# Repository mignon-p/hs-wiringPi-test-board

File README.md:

This is a simple add-on board for [Raspberry Pi][1].  It is meant for
testing the [Haskell binding for wiringPi][2].  It connects to the
Raspberry Pi via a 40-pin ribbon cable, and has the following
features:

* [wiringPi pins][3] 0-7 are connected to yellow LEDs

* wiringPi pins 26 and 23 are connected to red LEDs

* wiringPi pins 21 and 22 are connected to each other (via a resistor
  to prevent short circuits) to allow for automated testing (i. e. an
  output pin sending to an input pin)

* wiringPi pin 25 is connected to a momentary pushbutton which pulls
  it to ground via a resistor (so pin should be configured with an
  internal pullup)

The LEDs are driven [with transistors][4] from the 5V supply, to avoid
overloading the 3.3V supply.

This circuit board was designed with [KiCad][5], and was designed to
be fabricated with [OSH Park][6].

* [View schematic](schematic.pdf)
* [View PCB layout][9]
* [Order PCB from Osh Park][10] ($27.40 for three copies of the board,
  and free shipping)

See `digi-key.csv` for Bill of Materials with [Digi-Key][7] part
numbers.  With the 33 ohm resistors, the LEDs are really bright, so
you might want to substitute 68 ohm resistors instead.

This repository is licensed under the
[Creative Commons Attribution-ShareAlike 4.0 International license][8].

[1]: https://www.raspberrypi.org/
[2]: https://hackage.haskell.org/package/wiringPi
[3]: https://pinout.xyz/pinout/wiringpi
[4]: https://electronics.stackexchange.com/questions/60865/how-to-drive-a-20ma-led-from-a-4ma-max-gpio-pin#60868
[5]: http://kicad.org/
[6]: https://oshpark.com/
[7]: https://www.digikey.com/
[8]: https://creativecommons.org/licenses/by-sa/4.0/
[9]: https://eyrie.io/board/922367d680304403abe881f246e2a430
[10]: https://oshpark.com/shared_projects/bw71UDHZ

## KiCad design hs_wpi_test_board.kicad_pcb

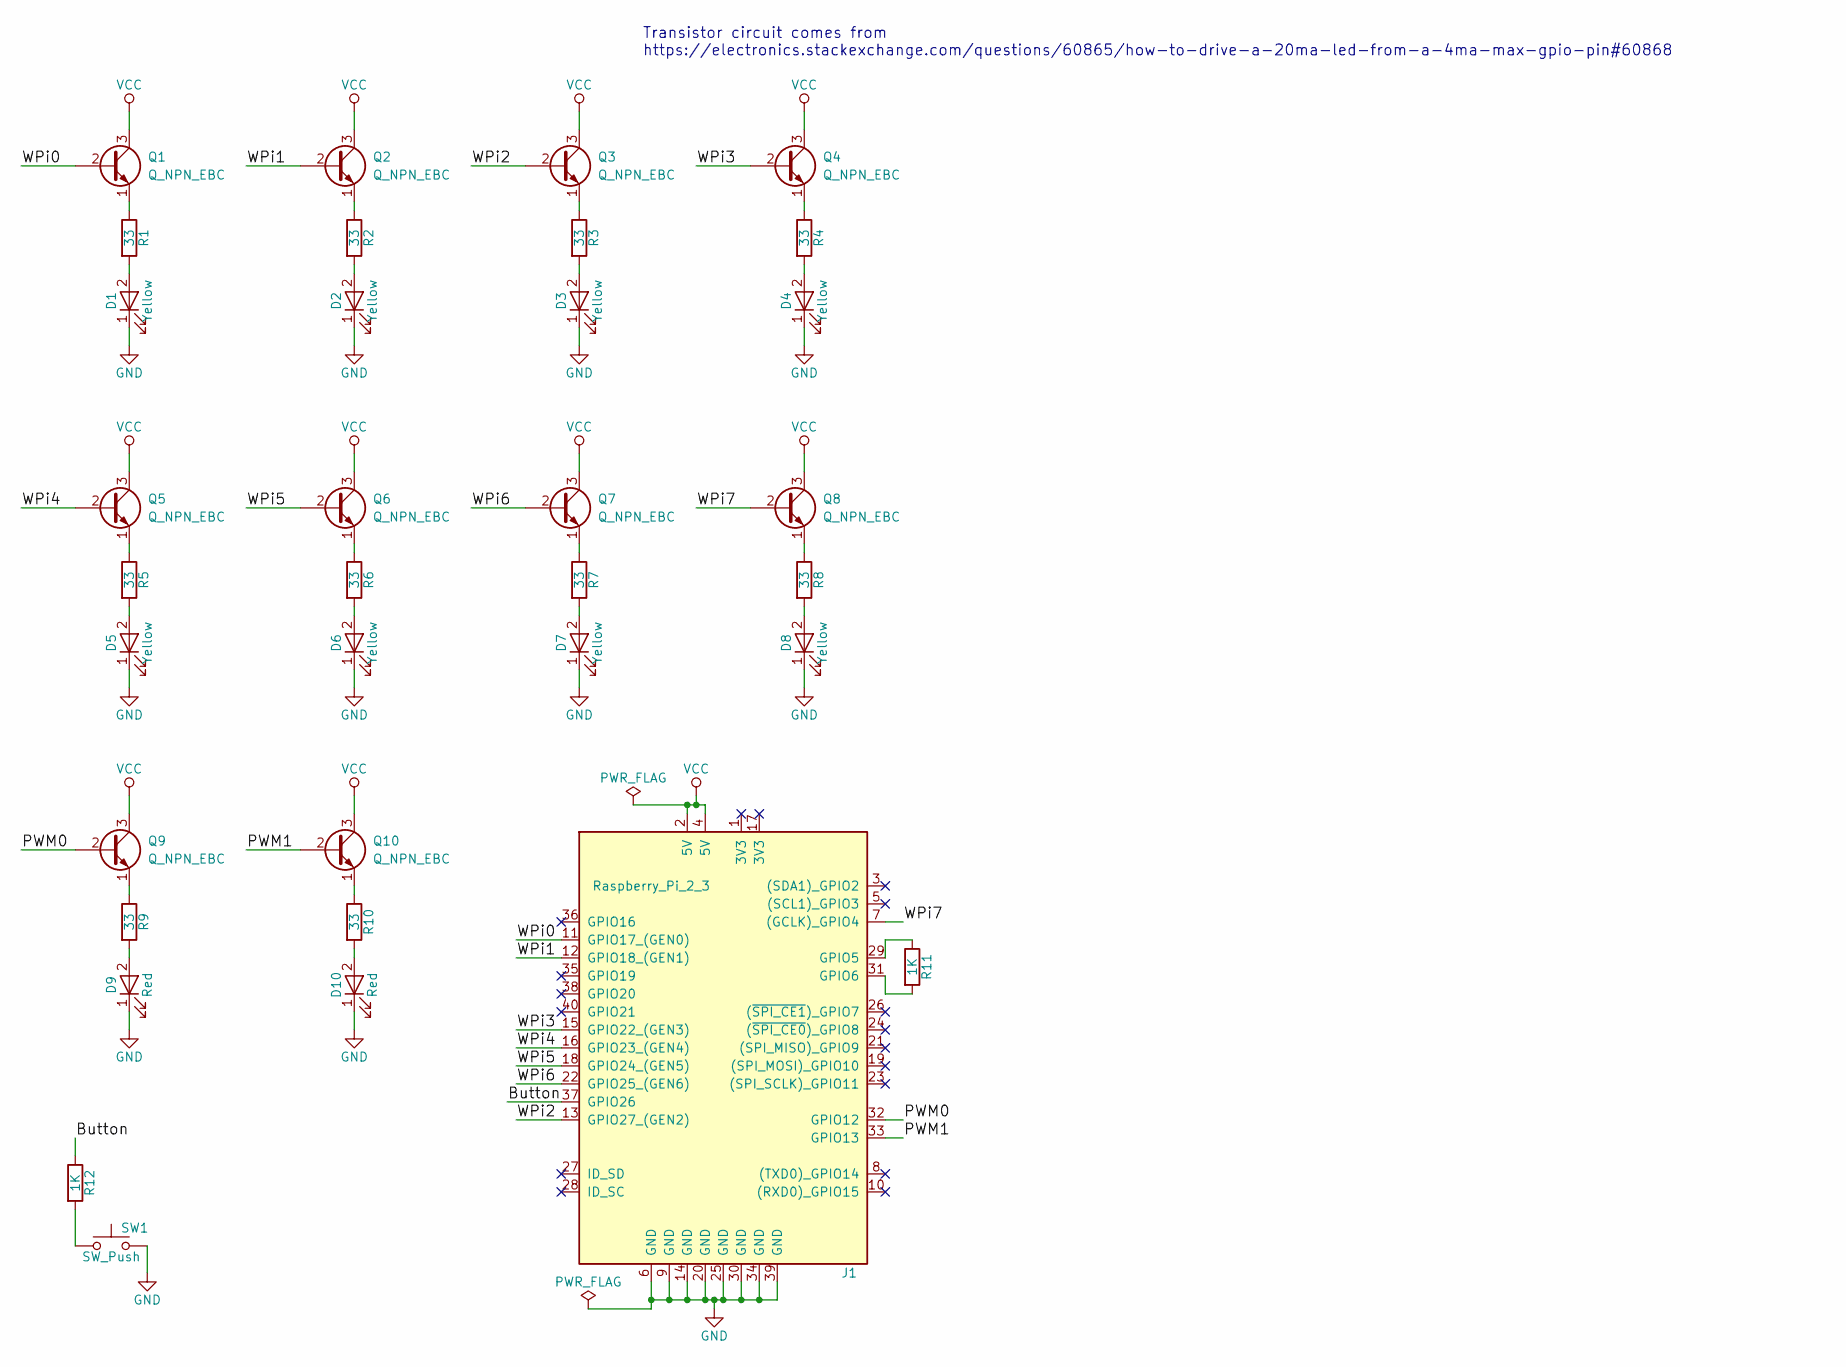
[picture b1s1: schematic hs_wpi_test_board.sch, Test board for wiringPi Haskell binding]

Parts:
D1, D2, D3, D4, D5, D6, D7, D8: Yellow; LED_D5.0mm
D9, D10: Red; LED_D5.0mm
J1: Raspberry_Pi_2_3; IDC_Header_Straight_40pins
Q1, Q2, Q3, Q4, Q5, Q6, Q7, Q8, Q9, Q10: Q_NPN_EBC; TO-92_Inline_Wide
R1, R2, R3, R4, R5, R6, R7, R8, R9, R10: 33; R_Axial_DIN0207_L6.3mm_D2.5mm_P10.16mm_Horizontal
R11, R12: 1K; R_Axial_DIN0207_L6.3mm_D2.5mm_P10.16mm_Horizontal
SW1: SW_Push; SW_PUSH-12mm_Wurth-430476085716

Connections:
/Button: J1.37 (GPIO26), R12.1
/PWM0: J1.32 (GPIO12), Q9.2 (B)
/PWM1: J1.33 (GPIO13), Q10.2 (B)
/WPi0: J1.11 (GPIO17_(GEN0)), Q1.2 (B)
/WPi1: J1.12 (GPIO18_(GEN1)), Q2.2 (B)
/WPi2: J1.13 (GPIO27_(GEN2)), Q3.2 (B)
/WPi3: J1.15 (GPIO22_(GEN3)), Q4.2 (B)
/WPi4: J1.16 (GPIO23_(GEN4)), Q5.2 (B)
/WPi5: J1.18 (GPIO24_(GEN5)), Q6.2 (B)
/WPi6: J1.22 (GPIO25_(GEN6)), Q7.2 (B)
/WPi7: J1.7 ((GCLK)_GPIO4), Q8.2 (B)
GND: D1.1 (K), D2.1 (K), D3.1 (K), D4.1 (K), D5.1 (K), D6.1 (K), D7.1 (K), D8.1 (K), D9.1 (K), D10.1 (K), J1.6 (GND), J1.9 (GND), J1.14 (GND), J1.20 (GND), J1.25 (GND), J1.30 (GND), J1.34 (GND), J1.39 (GND), SW1.2
unnamed: D1.2 (A), R1.2
unnamed: D2.2 (A), R2.2
unnamed: D3.2 (A), R3.2
unnamed: D4.2 (A), R4.2
unnamed: D5.2 (A), R5.2
unnamed: D6.2 (A), R6.2
unnamed: D7.2 (A), R7.2
unnamed: D8.2 (A), R8.2
unnamed: D9.2 (A), R9.2
unnamed: D10.2 (A), R10.2
unnamed: J1.29 (GPIO5), R11.1
unnamed: J1.31 (GPIO6), R11.2
unnamed: Q1.1 (E), R1.1
unnamed: Q2.1 (E), R2.1
unnamed: Q3.1 (E), R3.1
unnamed: Q4.1 (E), R4.1
unnamed: Q5.1 (E), R5.1
unnamed: Q6.1 (E), R6.1
unnamed: Q7.1 (E), R7.1
unnamed: Q8.1 (E), R8.1
unnamed: Q9.1 (E), R9.1
unnamed: Q10.1 (E), R10.1
unnamed: R12.2, SW1.1
VCC: J1.2 (5V), J1.4 (5V), Q1.3 (C), Q2.3 (C), Q3.3 (C), Q4.3 (C), Q5.3 (C), Q6.3 (C), Q7.3 (C), Q8.3 (C), Q9.3 (C), Q10.3 (C)

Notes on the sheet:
Transistor circuit comes from https://electronics.stackexchange.com/questions/60865/how-to-drive-a-20ma-led-from-a-4ma-max-gpio-pin#60868

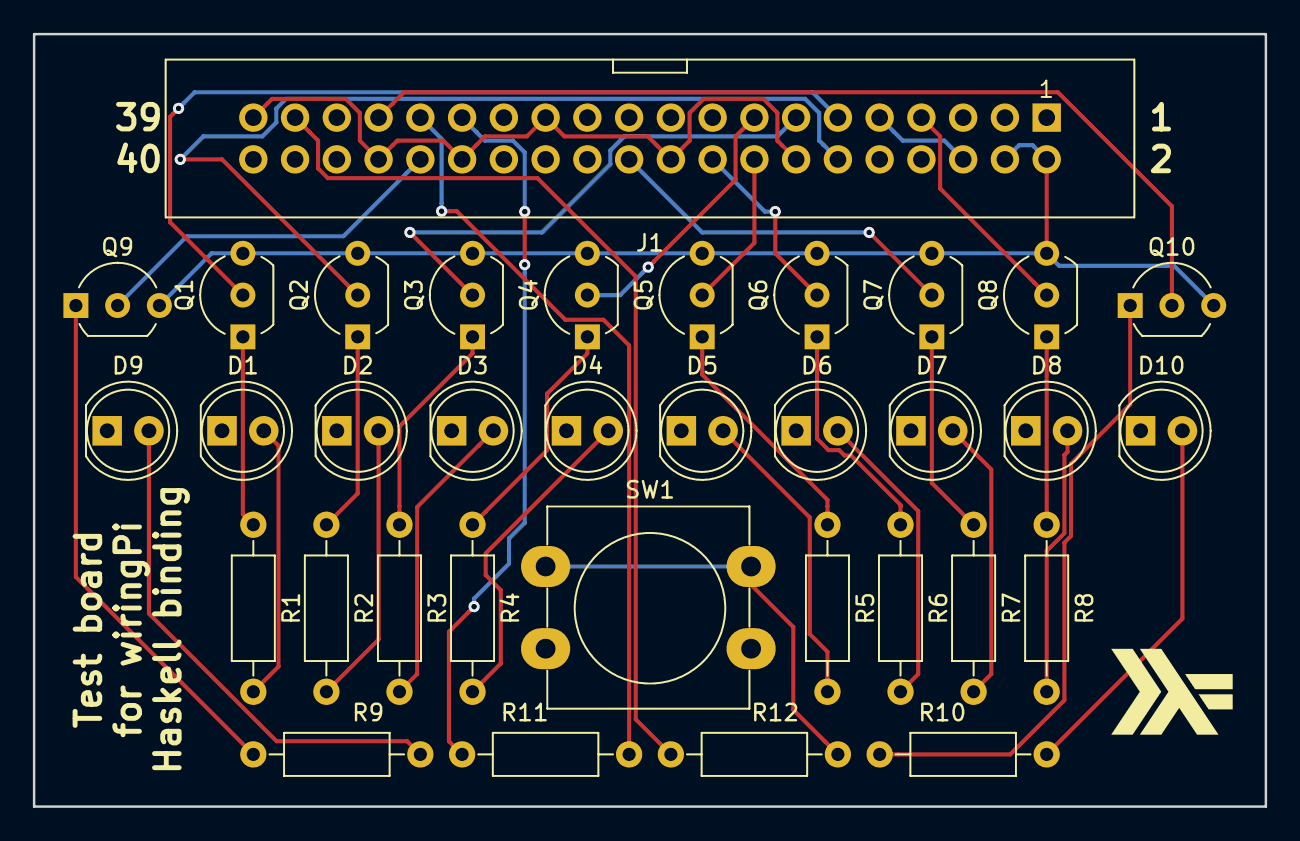
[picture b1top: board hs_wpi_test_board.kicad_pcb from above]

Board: 2 copper layers, 74.9 x 47.0 mm, 34 parts (0 on the bottom side), 36 nets.

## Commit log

2017-08-07 add power flags and no connects
2017-08-07 associate footprints
2017-08-07 imported netlist
2017-08-07 change footprint for J1
2017-08-07 angled socket
2017-08-07 pin header straight
2017-08-07 place components
2017-08-07 add board outline
2017-08-07 routed some stuff
2017-08-07 finished board
2017-08-07 switch J1 footprint to Connectors:IDC_Header_Straight_40pins
2017-08-08 add feet on silkscreen
2017-08-08 remove all routing
2017-08-08 switch to wider footprint for transistors
2017-08-08 work in progress
2017-08-08 position footprints
2017-08-08 draw board outline
2017-08-08 finish routing
2017-08-08 silkscreen text
2017-08-08 not sure where that came from
2017-08-08 add Haskell logo footprint
2017-08-08 add Haskell logo to board
2017-08-08 move some vias around to avoid silkscreen
2017-08-08 adjust resistor silkscreen locations
2017-08-08 update Haskell logo footprint with pretty-printing and timestamp
2017-08-08 add some text to schematic
2017-08-08 add documentation
2017-08-08 update text on silkscreen
2017-08-08 add KiCad and OSHW logos to back silkscreen
2017-08-08 more drawings on silkscreen to indicate position of J1
2017-08-23 Like IDC_Header_Straight_40pins from library, but with notch on silkscreen.
    This makes it clearer which way the connector should go.
2017-08-23 push button footprint with bigger holes
2017-08-23 make board a little larger
2017-08-23 allow better connections to ground plane from more pins
2017-08-23 use connector footprint with notch on silkscreen
2017-08-23 use new button footprint
2017-09-07 unknown changes to hs_wpi_test_board.pro
2017-09-07 change soldermask clearance to 2 mils
    I was getting shorts, and OSH Park said:
    "Oh, the easy fix here is to reduce your mask expansion. We recommend
    2 mil. When the mask expansion is larger than this, it can sometimes
    wind up exposing nearby traces. It's sadly a problem that design tools
    don't really warn you about, and a lot of folks simply have to
    discover this on their own."
2017-09-07 add photo of board
2017-09-07 update date and revision
2017-10-05 Add schematic PDF, and links to Eyrie and OSH Park.
2021-10-22 Link to kicad.org
    https://forum.kicad.info/t/warning-avoid-all-links-to-kicad-pcb-org-use-kicad-org/31521
